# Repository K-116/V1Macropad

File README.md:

# K116's hackpad 
this is my hackpad for blueprint, I added an oled, button and rotary encoder to the project. I used FreeCad and Tinkercad instead on Fusion360 the project file is avaliable <a href="https://github.com/K-116/V1Macropad/blob/main/CAD/k116finalproject.FCStd">here</a>

<h2>Here is a my 3d design</h2>

<h2>Schematic and PCB</h2>

<h2>Main takeaways</h2>
This project was definitely a learning experience, this was my first ever pcb and was my first time ever using KICAD. Although the tutorial used fusion 360, I learned that FreeCAD was much easier for me so I used that. I watched alot of Youtube videos to get the basics of KICAD (schematics, matrix, pcb routing) although connecting the 3d models to the components was a great challenge.

The main goal I had in mind was to make a Macropad that could adjust volume with the rotary encoder, link to youtube videos/music with the top two keys and copy,paste &select all with the bottom three. I designed the case to expose the pcb as I like to see my work and so I could fix any issues. :)

<h2>Final</h2>
I will make an additional section when I get the macropad!

made with ❤️ for blueprint

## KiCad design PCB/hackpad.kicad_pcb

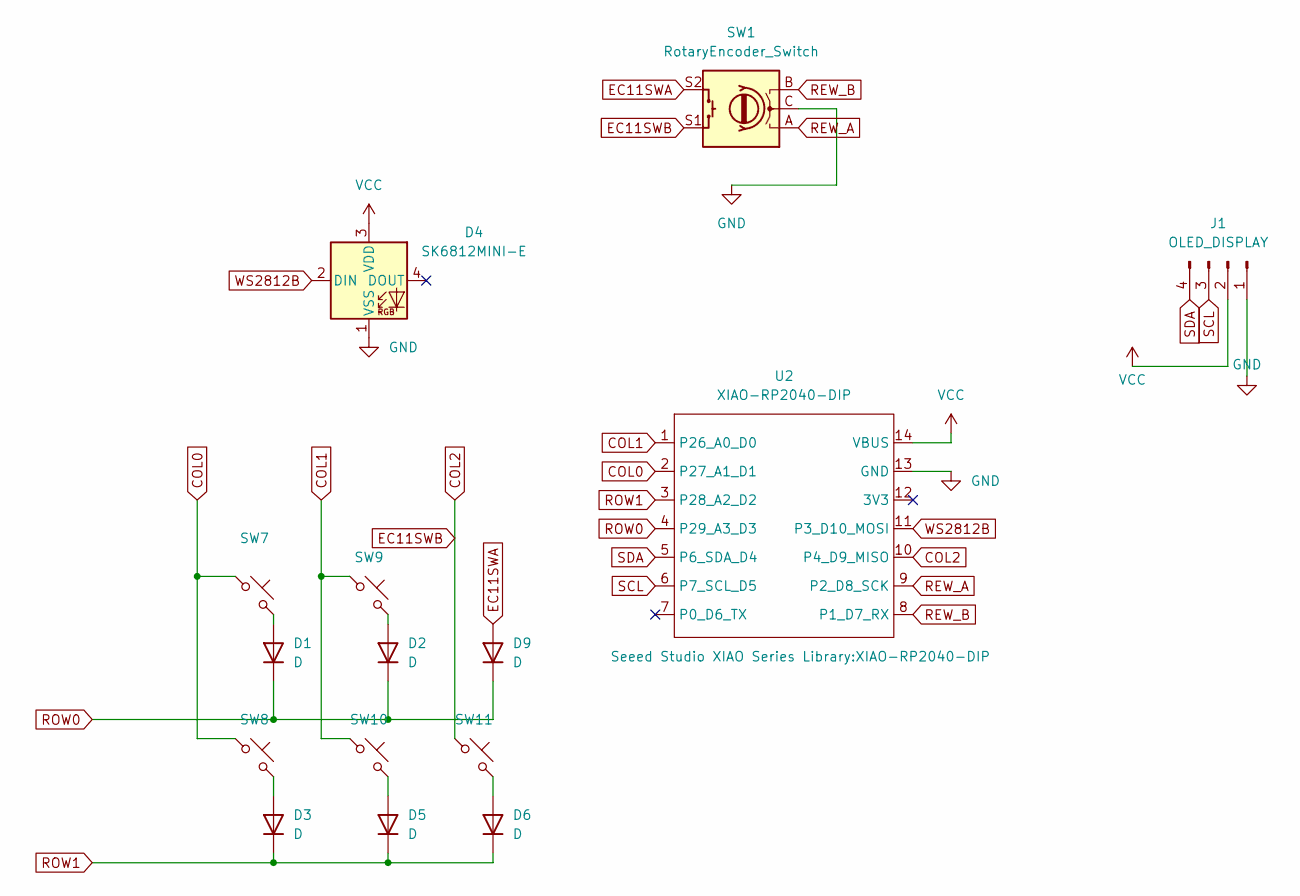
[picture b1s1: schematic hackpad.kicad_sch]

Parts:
D1, D2, D3, D5, D6, D9: D; D_DO-35_SOD27_P7.62mm_Horizontal
D4: SK6812MINI-E; SK6812MINI-E_fixed
J1: OLED_DISPLAY; SSD1306-0.91-OLED-4pin-128x32(1)
SW1: RotaryEncoder_Switch; RotaryEncoder_Alps_EC11E-Switch_Vertical_H20mm
SW7, SW8, SW9, SW10, SW11: SW_Push_45deg; SW_Cherry_MX_1.00u_PCB
U2: XIAO-RP2040-DIP

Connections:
COL0: SW7.1, SW8.1, U2.2 (P27_A1_D1)
COL1: SW9.1, SW10.1, U2.1 (P26_A0_D0)
COL2: SW1.S1, SW11.1, U2.10 (P4_D9_MISO)
EC11SWA: D9.2 (A), SW1.S2
GND: D4.1 (VSS), J1.1, SW1.C, U2.13 (GND)
unnamed: D1.2 (A), SW7.2
unnamed: D2.2 (A), SW9.2
unnamed: D3.2 (A), SW8.2
unnamed: D5.2 (A), SW10.2
unnamed: D6.2 (A), SW11.2
REW_A: SW1.A, U2.9 (P2_D8_SCK)
REW_B: SW1.B, U2.8 (P1_D7_RX)
ROW0: D1.1 (K), D2.1 (K), D9.1 (K), U2.4 (P29_A3_D3)
ROW1: D3.1 (K), D5.1 (K), D6.1 (K), U2.3 (P28_A2_D2)
SCL: J1.3, U2.6 (P7_SCL_D5)
SDA: J1.4, U2.5 (P6_SDA_D4)
VCC: D4.3 (VDD), J1.2, U2.14 (VBUS)
WS2812B: D4.2 (DIN), U2.11 (P3_D10_MOSI)

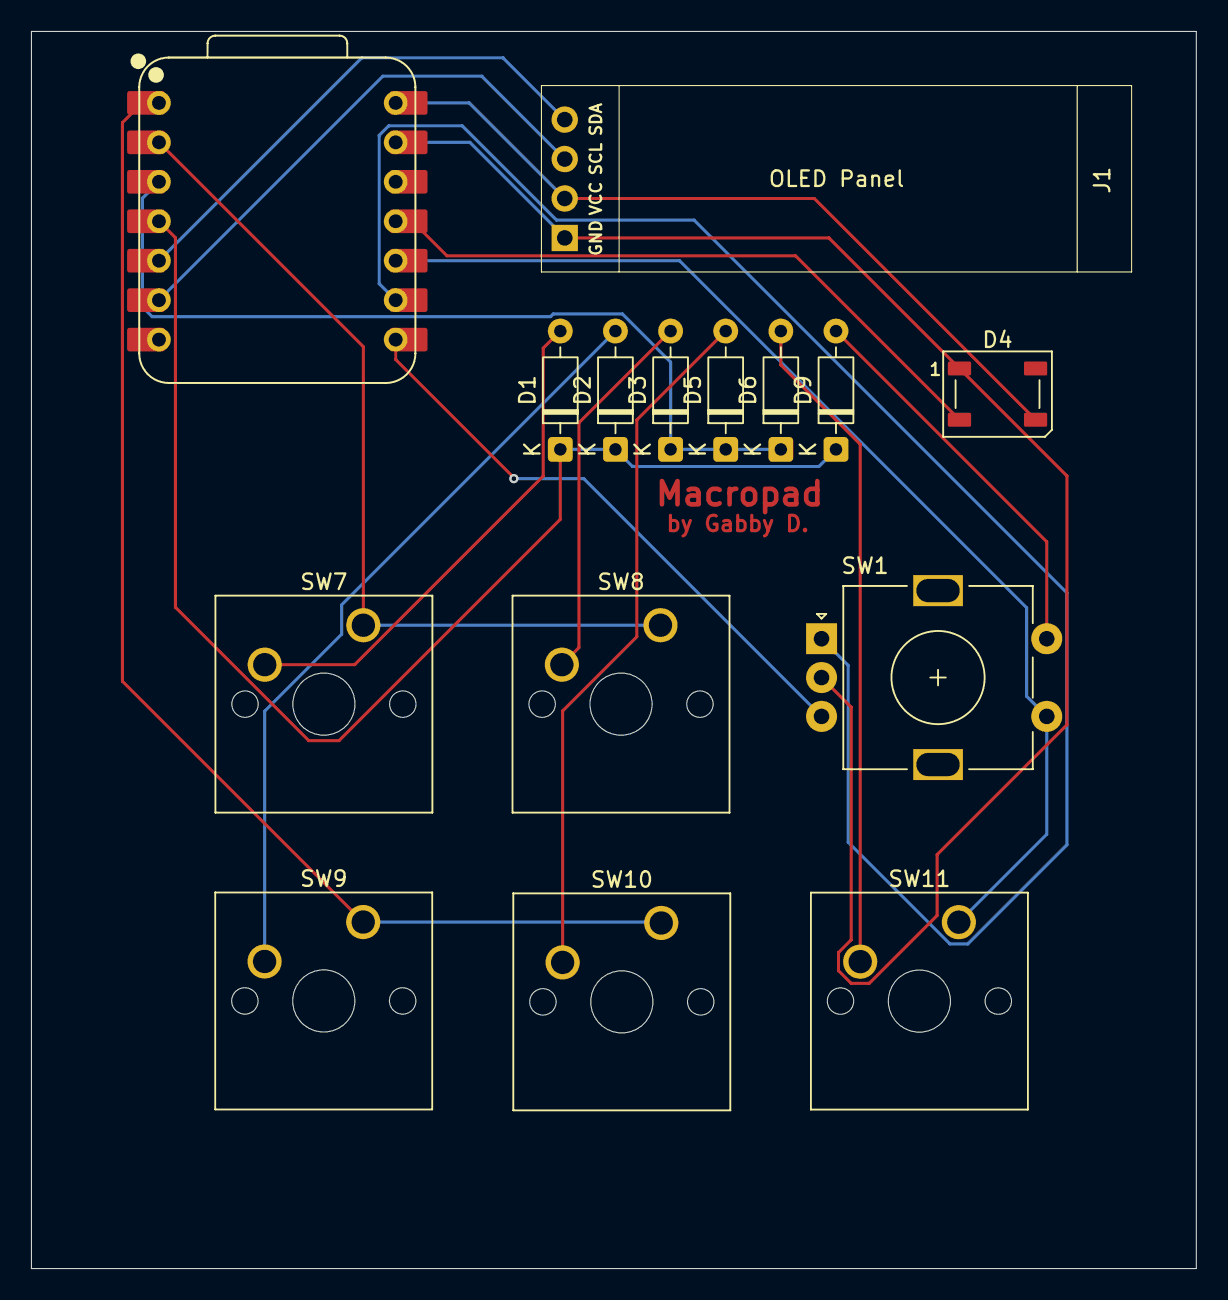
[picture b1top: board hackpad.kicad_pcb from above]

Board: 2 copper layers, 75.0 x 79.7 mm, 15 parts (0 on the bottom side), 18 nets.

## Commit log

2026-03-24 Create pcb
2026-03-24 Create hackpad
2026-03-24 Create 3d
2026-03-26 Initialize keyboard with hardware configuration
    Set up keyboard configuration with encoder and RGB support.
2026-03-26 Add new image to README.md
2026-03-26 Added STEP file
2026-03-26 Configure LFS for STEP files
2026-03-26 Add K116 Hackpad STEP file
2026-03-26 Rename K116-Hackpad.step to CAD/K116-Hackpad.step
2026-03-29 Create -
2026-03-29 Enhance README with Onshape links and images
    Updated README with additional links and images for the project.
2026-03-29 Revise README with project details and links
    Updated project description and added FreeCad information.
2026-03-29 Update README with project file link
    Added a link to the project file in FreeCad.
2026-03-30 Rename k116finalproject.FCStd to CAD/k116finalproject.FCStd
2026-03-31 Fix project file link in README
    Updated the project file link to point to the correct location in the repository.
2026-04-02 Refactor keyboard configuration and add YouTube macro
